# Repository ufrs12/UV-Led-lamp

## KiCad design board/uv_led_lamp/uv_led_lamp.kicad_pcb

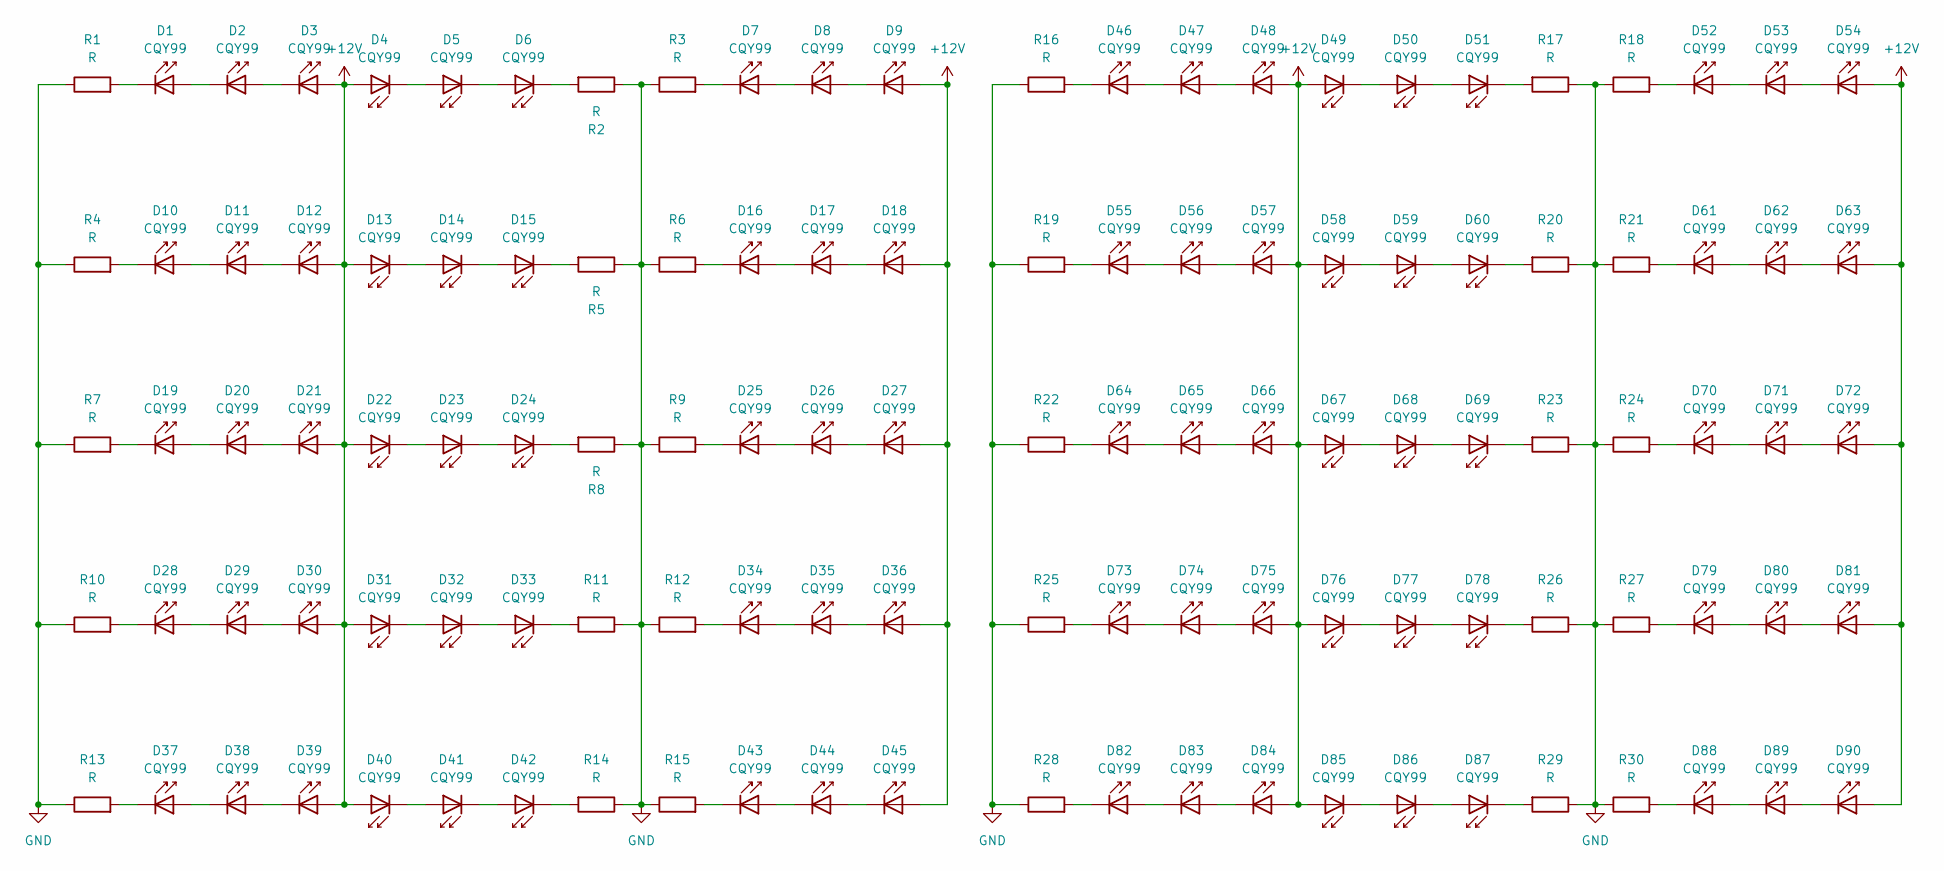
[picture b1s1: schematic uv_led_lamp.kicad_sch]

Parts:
D1, D2, D3, D4, D5, D6, D7, D8, D9, D10, D11, D12, D13, D14, D15, D16, D17, D18, D19, D20, D21, D22, D23, D24, D25, D26, D27, D28, D29, D30, D31, D32, D33, D34, D35, D36, D37, D38, D39, D40, D41, D42, D43, D44, D45, D46, D47, D48, D49, D50, D51, D52, D53, D54, D55, D56, D57, D58, D59, D60, D61, D62, D63, D64, D65, D66, D67, D68, D69, D70, D71, D72, D73, D74, D75, D76, D77, D78, D79, D80, D81, D82, D83, D84, D85, D86, D87, D88, D89, D90: CQY99; LED_D5.0mm_IRGrey
R1, R2, R3, R4, R5, R6, R7, R8, R9, R10, R11, R12, R13, R14, R15, R16, R17, R18, R19, R20, R21, R22, R23, R24, R25, R26, R27, R28, R29, R30: R; R_Axial_DIN0207_L6.3mm_D2.5mm_P10.16mm_Horizontal

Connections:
+12V: D3.2 (A), D4.2 (A), D9.2 (A), D12.2 (A), D13.2 (A), D18.2 (A), D21.2 (A), D22.2 (A), D27.2 (A), D30.2 (A), D31.2 (A), D36.2 (A), D39.2 (A), D40.2 (A), D45.2 (A), D48.2 (A), D49.2 (A), D54.2 (A), D57.2 (A), D58.2 (A), D63.2 (A), D66.2 (A), D67.2 (A), D72.2 (A), D75.2 (A), D76.2 (A), D81.2 (A), D84.2 (A), D85.2 (A), D90.2 (A)
GND: R1.1, R2.1, R3.1, R4.1, R5.1, R6.1, R7.1, R8.1, R9.1, R10.1, R11.1, R12.1, R13.1, R14.1, R15.1, R16.1, R17.1, R18.1, R19.1, R20.1, R21.1, R22.1, R23.1, R24.1, R25.1, R26.1, R27.1, R28.1, R29.1, R30.1
unnamed: D1.2 (A), D2.1 (K)
unnamed: D1.1 (K), R1.2
unnamed: D2.2 (A), D3.1 (K)
unnamed: D4.1 (K), D5.2 (A)
unnamed: D5.1 (K), D6.2 (A)
unnamed: D6.1 (K), R2.2
unnamed: D7.2 (A), D8.1 (K)
unnamed: D7.1 (K), R3.2
unnamed: D8.2 (A), D9.1 (K)
unnamed: D10.2 (A), D11.1 (K)
unnamed: D10.1 (K), R4.2
unnamed: D11.2 (A), D12.1 (K)
unnamed: D13.1 (K), D14.2 (A)
unnamed: D14.1 (K), D15.2 (A)
unnamed: D15.1 (K), R5.2
unnamed: D16.2 (A), D17.1 (K)
unnamed: D16.1 (K), R6.2
unnamed: D17.2 (A), D18.1 (K)
unnamed: D19.2 (A), D20.1 (K)
unnamed: D19.1 (K), R7.2
unnamed: D20.2 (A), D21.1 (K)
unnamed: D22.1 (K), D23.2 (A)
unnamed: D23.1 (K), D24.2 (A)
unnamed: D24.1 (K), R8.2
unnamed: D25.2 (A), D26.1 (K)
unnamed: D25.1 (K), R9.2
unnamed: D26.2 (A), D27.1 (K)
unnamed: D28.2 (A), D29.1 (K)
unnamed: D28.1 (K), R10.2
unnamed: D29.2 (A), D30.1 (K)
unnamed: D31.1 (K), D32.2 (A)
unnamed: D32.1 (K), D33.2 (A)
unnamed: D33.1 (K), R11.2
unnamed: D34.2 (A), D35.1 (K)
unnamed: D34.1 (K), R12.2
unnamed: D35.2 (A), D36.1 (K)
unnamed: D37.2 (A), D38.1 (K)
unnamed: D37.1 (K), R13.2
unnamed: D38.2 (A), D39.1 (K)
unnamed: D40.1 (K), D41.2 (A)
unnamed: D41.1 (K), D42.2 (A)
unnamed: D42.1 (K), R14.2
unnamed: D43.2 (A), D44.1 (K)
unnamed: D43.1 (K), R15.2
unnamed: D44.2 (A), D45.1 (K)
unnamed: D46.2 (A), D47.1 (K)
unnamed: D46.1 (K), R16.2
unnamed: D47.2 (A), D48.1 (K)
unnamed: D49.1 (K), D50.2 (A)
unnamed: D50.1 (K), D51.2 (A)
unnamed: D51.1 (K), R17.2
unnamed: D52.2 (A), D53.1 (K)
unnamed: D52.1 (K), R18.2
unnamed: D53.2 (A), D54.1 (K)
unnamed: D55.2 (A), D56.1 (K)
unnamed: D55.1 (K), R19.2
unnamed: D56.2 (A), D57.1 (K)
unnamed: D58.1 (K), D59.2 (A)
unnamed: D59.1 (K), D60.2 (A)
unnamed: D60.1 (K), R20.2
unnamed: D61.2 (A), D62.1 (K)
unnamed: D61.1 (K), R21.2
unnamed: D62.2 (A), D63.1 (K)
unnamed: D64.2 (A), D65.1 (K)
unnamed: D64.1 (K), R22.2
unnamed: D65.2 (A), D66.1 (K)
unnamed: D67.1 (K), D68.2 (A)
unnamed: D68.1 (K), D69.2 (A)
unnamed: D69.1 (K), R23.2
unnamed: D70.2 (A), D71.1 (K)
unnamed: D70.1 (K), R24.2
unnamed: D71.2 (A), D72.1 (K)
unnamed: D73.2 (A), D74.1 (K)
unnamed: D73.1 (K), R25.2
unnamed: D74.2 (A), D75.1 (K)
unnamed: D76.1 (K), D77.2 (A)
unnamed: D77.1 (K), D78.2 (A)
unnamed: D78.1 (K), R26.2
unnamed: D79.2 (A), D80.1 (K)
unnamed: D79.1 (K), R27.2
unnamed: D80.2 (A), D81.1 (K)
unnamed: D82.2 (A), D83.1 (K)
unnamed: D82.1 (K), R28.2
unnamed: D83.2 (A), D84.1 (K)
unnamed: D85.1 (K), D86.2 (A)
unnamed: D86.1 (K), D87.2 (A)
unnamed: D87.1 (K), R29.2
unnamed: D88.2 (A), D89.1 (K)
unnamed: D88.1 (K), R30.2
unnamed: D89.2 (A), D90.1 (K)

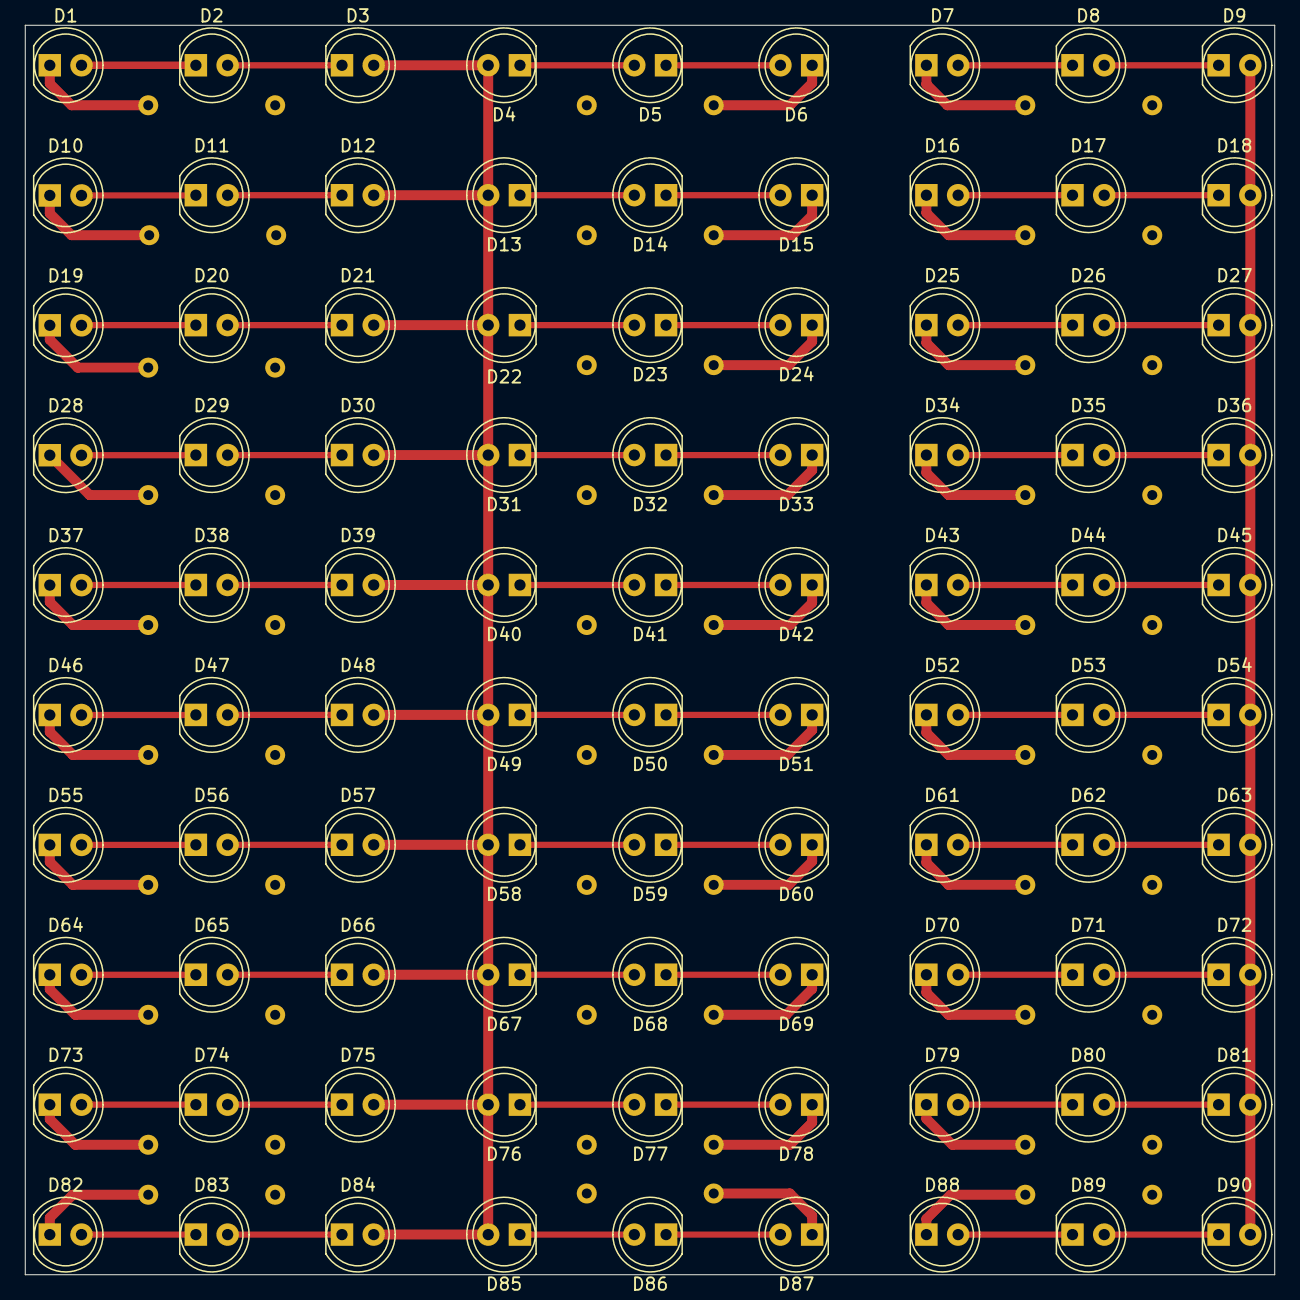
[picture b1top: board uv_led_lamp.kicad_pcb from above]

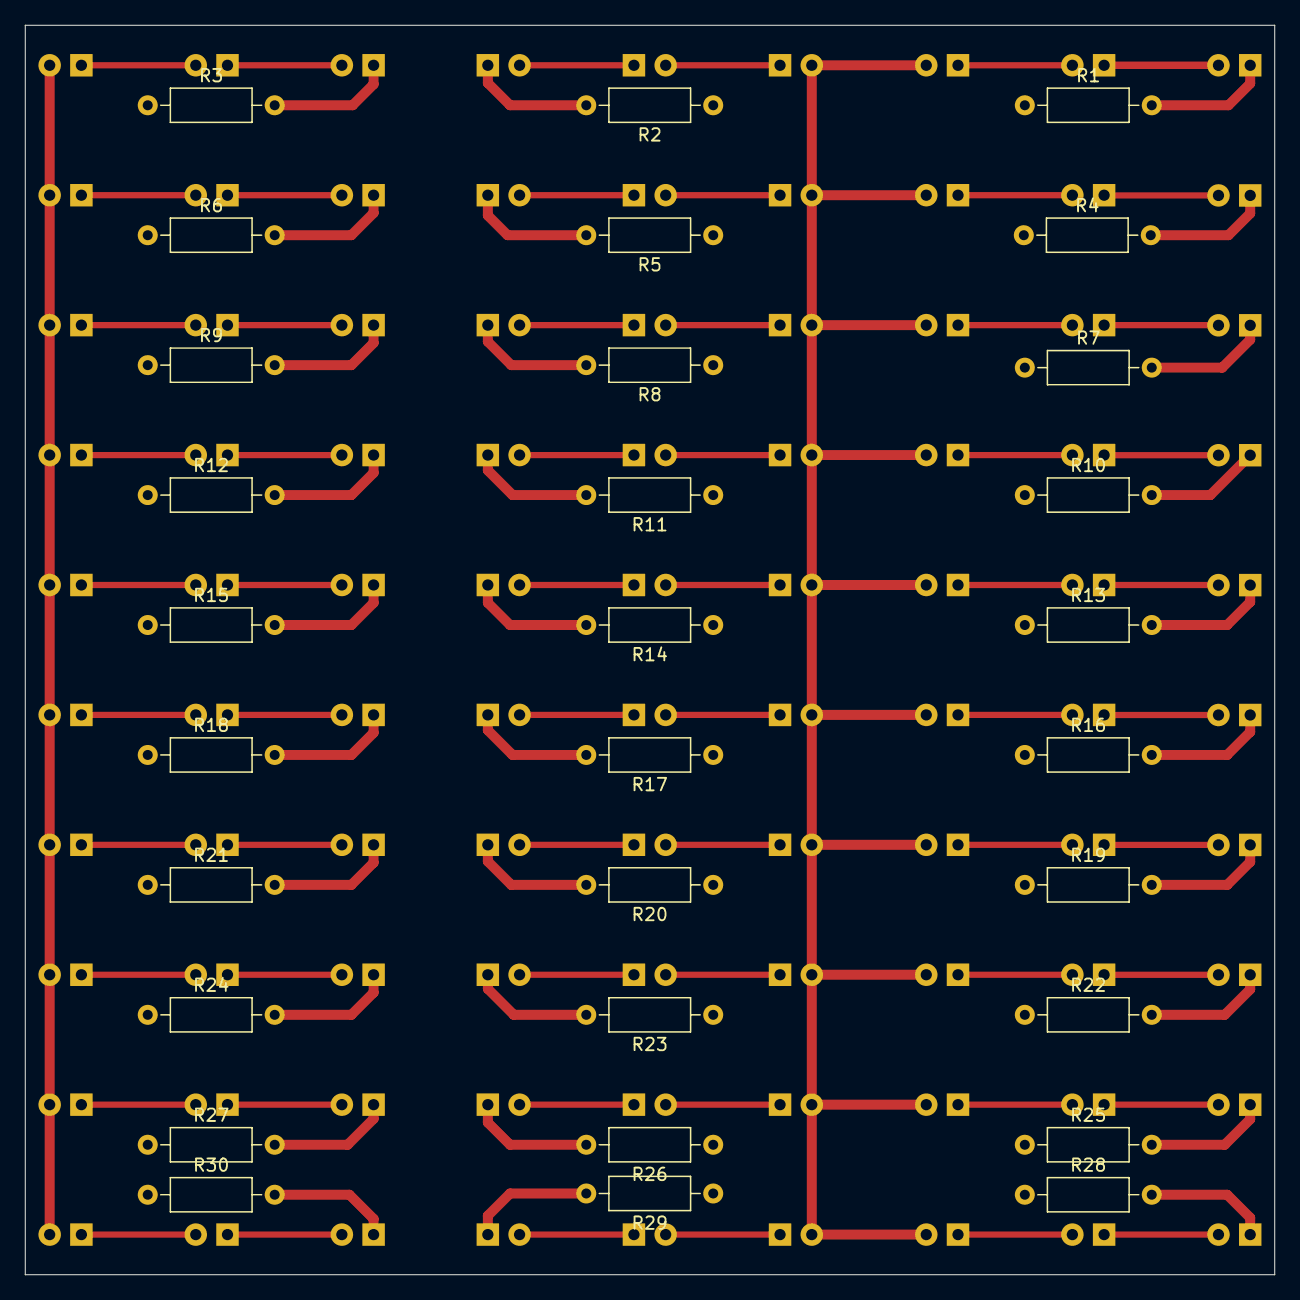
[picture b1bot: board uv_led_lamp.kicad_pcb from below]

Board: 2 copper layers, 100.0 x 100.0 mm, 120 parts (30 on the bottom side), 92 nets.
